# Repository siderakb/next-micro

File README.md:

# Next *μ*

**Next *μ*** or **Next Micro** is a Pro Micro/[Elite-C](https://deskthority.net/wiki/Elite-C) compatible ATmega32U4 board, specialized design for keyboards.

It has mid-mount USB Type-C and more available pins (25 pins, all pins of ATmega32U4 except `PE2/HWB`) than both Pro Micro (18 pins) and Elite-C (24 pins).  
The on-board RESET button makes development easier.

> A part of [ErgoSNM keyboard](https://github.com/siderakb/ergo-snm-keyboard) project.  

## Preview

| Front                           | Back                           | Layers                    |
| ------------------------------- | ------------------------------ | ------------------------- |
|  |  |  |

## Pinouts
| Func | 32U4  | L <-> R |  32U4 | Func |
| :--- | :---- | :-----: | ----: | ---: |
|      | PB7\* |         |   PB0 |      |
| TX   | PD3   |         |   RAW |      |
| RX   | PD2   |         |   GND |      |
|      | GND   |         | RESET |      |
|      | GND   |         |   VCC |      |
| SDA  | PD1   |         |   PF4 |   A3 |
| SCL  | PD0\* |         |   PF5 |   A2 |
| A6   | PD4   |         |   PF6 |   A1 |
|      | PC6\* |         |   PF7 |   A0 |
| A7   | PD7\* |         |   PB1 | SCLK |
|      | PE6   |         |   PB3 | MISO |
| A8   | PB4   |         |   PB2 | MOSI |
| A9   | PB5\* |         | PB6\* |  A10 |

Bottom row from left to right: PD6, PD5, PC7\*, PF1, PF0.

- The pin marked with `*` can output PWM.
- RAW: LDO Vin pin.

> The pinouts not fully compatible with Elite-C.

## Jumper Config

- JP1: LDO bypass.
  - Open: VCC is 3.3V (LDO Vout).
  - Closed: VCC is 5V (VBUS or RAW). 

## BOM

| Designator  | Value                   | Footprint                           |
| ----------- | ----------------------- | ----------------------------------- |
| C1,C2       | 20pF                    | 0402 (1005 Metric)                  |
| C3,C6,C7    | 100nF                   | 0402 (1005 Metric)                  |
| C4,C5,C8,C9 | 1uF                     | 0402 (1005 Metric)                  |
| D1          | B5817                   | SOD-323                             |
| F1          | 500mA, 6V               | 0805 (2012 Metric)                  |
| J1          | USB_C_Receptacle_USB2.0 | 918-418K2024S40000                  |
| R1,R2       | 5.1k                    | 0402 (1005 Metric)                  |
| R3,R4       | 22                      | 0402 (1005 Metric)                  |
| R5          | 10k                     | 0402 (1005 Metric)                  |
| SW1         | RESET                   | B3U-1000P                           |
| U1          | ATmega32U4-M            | QFN-44-1EP 7x7mm P0.5mm EP5.2x5.2mm |
| U2          | RT9013-33GB             | SOT-23-5                            |
| Y1          | 8MHz                    | 2Pin 5x3.2mm                        |
> See also [`doc/next-micro_bom.csv`](./doc/next-micro_bom.csv).

There is not designator silkscreen on PCB, please use your browser to open the `ibom.html` file (placed in [release page][release] and [`doc/`](./doc/)) to refer to the placement of the parts, it is generated by [Interactive HTML BOM](https://github.com/openscopeproject/InteractiveHtmlBom) plugin.

## PCBA

The BOM and CPL files for PCBA are placed in the [`doc/`](./doc/) folder and [release page][release].

## Board Characteristics

- Copper layer count: 2
- Board thickness: 1.6 mm
- Board overall dimensions: 17.78 x 33.02 mm (0.7 x 1.3 inch)
- Min track/spacing: 0.13 mm / 0.13 mm
- Min hole diameter: 0.3 mm
- Castellated pads: No
- Edge card connectors: No
- Plated board edge: No

## Disclaimer

These files without warranty of any kind, use at your own risk, it is recommended to check yourself before manufacture.

For the full statement, please see [LICENSE](./LICENSE).

[release]: https://github.com/ziteh/next-micro/releases

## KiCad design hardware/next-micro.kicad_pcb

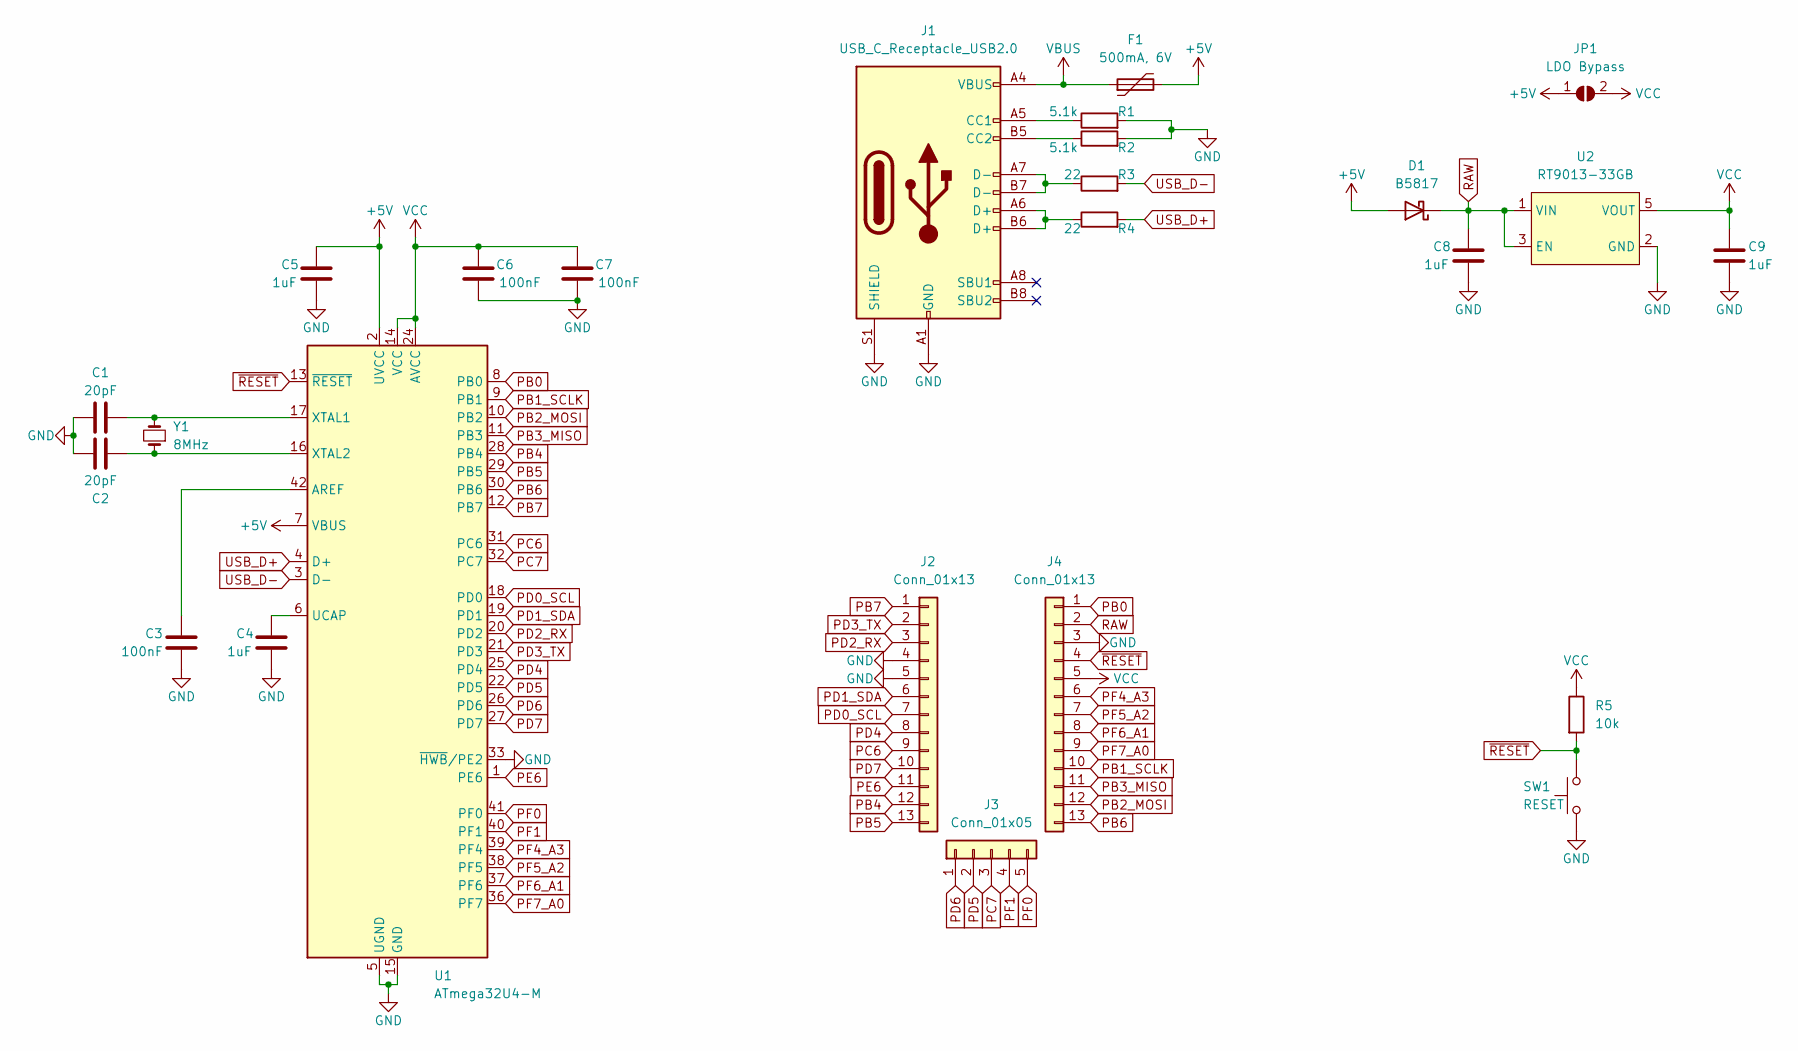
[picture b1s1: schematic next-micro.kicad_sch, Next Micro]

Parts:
C1, C2: 20pF; C_0402_1005Metric; MFR. Part # 0402CG200J500NT; JLCPCB Part # C1554
C3, C6, C7: 100nF; C_0402_1005Metric; MFR. Part # CL05B104KB54PNC; JLCPCB Part # C307331
C4, C5, C8, C9: 1uF; C_0402_1005Metric; MFR. Part # CL05A105KA5NQNC; JLCPCB Part # C52923
D1: B5817; D_SOD-323_HandSoldering; MFR. Part # B5817WS; JLCPCB Part # C123899
F1: 500mA, 6V; Fuse_0805_2012Metric; MFR. Part # SMD0805B050TF; JLCPCB Part # C269104
J1: USB_C_Receptacle_USB2.0; USB Type-C Mid-Mount Receptacle 16P; MFR. Part # 918-418K2024S40000; JLCPCB Part # C168688
J2, J4: Conn_01x13; PinHeader_1x13_P2.54mm_Vertical
J3: Conn_01x05; PinHeader_1x05_P2.54mm_Vertical
JP1: SolderJumper_2_Open; SolderJumper-2_P1.3mm_Open_TrianglePad1.0x1.5mm
R1, R2: 5.1k; R_0402_1005Metric; MFR. Part # 0402WGF5101TCE; JLCPCB Part # C25905
R3, R4: 22; R_0402_1005Metric; MFR. Part # 0402WGF220JTCE; JLCPCB Part # C25092
R5: 10k; R_0402_1005Metric; MFR. Part # 0402WGF1002TCE; JLCPCB Part # C25744
SW1: RESET; SW_SPST_B3U-1000P; MFR. Part # B3U-1000P; JLCPCB Part # C231329
U1: ATmega32U4-M; QFN-44-1EP_7x7mm_P0.5mm_EP5.2x5.2mm; MFR. Part # ATMEGA32U4-MU; JLCPCB Part # C112161
U2: RT9013-33GB; SOT-23-5; MFR. Part # RT9013-33GB; JLCPCB Part # C47773
Y1: 8MHz; Crystal_SMD_Qantek_QC5CB-2Pin_5x3.2mm; MFR. Part # X50328MSB2GI; JLCPCB Part # C115962

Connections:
+5V: C5.1, D1.2 (A), F1.2, JP1.1 (A), U1.2 (UVCC), U1.7 (VBUS)
GND: C1.1, C2.1, C3.1, C4.2, C5.2, C6.1, C7.1, C8.2, C9.2, J1.A1 (GND), J1.A12 (GND), J1.B1 (GND), J1.B12 (GND), J1.S1 (SHIELD), J2.4, J2.5, J4.3, R1.2, R2.2, SW1.1, U1.5 (UGND), U1.15 (GND), U1.23 (GND), U1.33 (~HWB/PE2), U1.35 (GND), U1.43 (GND), U1.45 (GND), U2.2 (GND)
unnamed: C1.2, U1.17 (XTAL1), Y1.2
unnamed: C2.2, U1.16 (XTAL2), Y1.1
unnamed: C3.2, U1.42 (AREF)
unnamed: C4.1, U1.6 (UCAP)
unnamed: J1.A5 (CC1), R1.1
unnamed: J1.A6 (D+), J1.B6 (D+), R4.1
unnamed: J1.A7 (D-), J1.B7 (D-), R3.1
unnamed: J1.B5 (CC2), R2.1
PB0: J4.1, U1.8 (PB0)
PB1_SCLK: J4.10, U1.9 (PB1)
PB2_MOSI: J4.12, U1.10 (PB2)
PB3_MISO: J4.11, U1.11 (PB3)
PB4: J2.12, U1.28 (PB4)
PB5: J2.13, U1.29 (PB5)
PB6: J4.13, U1.30 (PB6)
PB7: J2.1, U1.12 (PB7)
PC6: J2.9, U1.31 (PC6)
PC7: J3.3, U1.32 (PC7)
PD0_SCL: J2.7, U1.18 (PD0)
PD1_SDA: J2.6, U1.19 (PD1)
PD2_RX: J2.3, U1.20 (PD2)
PD3_TX: J2.2, U1.21 (PD3)
PD4: J2.8, U1.25 (PD4)
PD5: J3.2, U1.22 (PD5)
PD6: J3.1, U1.26 (PD6)
PD7: J2.10, U1.27 (PD7)
PE6: J2.11, U1.1 (PE6)
PF0: J3.5, U1.41 (PF0)
PF1: J3.4, U1.40 (PF1)
PF4_A3: J4.6, U1.39 (PF4)
PF5_A2: J4.7, U1.38 (PF5)
PF6_A1: J4.8, U1.37 (PF6)
PF7_A0: J4.9, U1.36 (PF7)
RAW: C8.1, D1.1 (K), J4.2, U2.1 (VIN), U2.3 (EN)
USB_D+: R4.2, U1.4 (D+)
USB_D-: R3.2, U1.3 (D-)
VBUS: F1.1, J1.A4 (VBUS), J1.A9 (VBUS), J1.B4 (VBUS), J1.B9 (VBUS)
VCC: C6.2, C7.2, C9.1, J4.5, JP1.2 (B), R5.1, U1.14 (VCC), U1.24 (AVCC), U1.34 (VCC), U1.44 (AVCC), U2.5 (VOUT)
~RESET: J4.4, R5.2, SW1.2, U1.13 (~RESET)

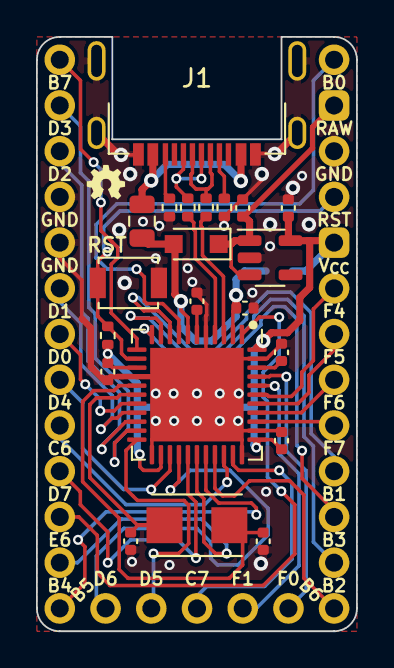
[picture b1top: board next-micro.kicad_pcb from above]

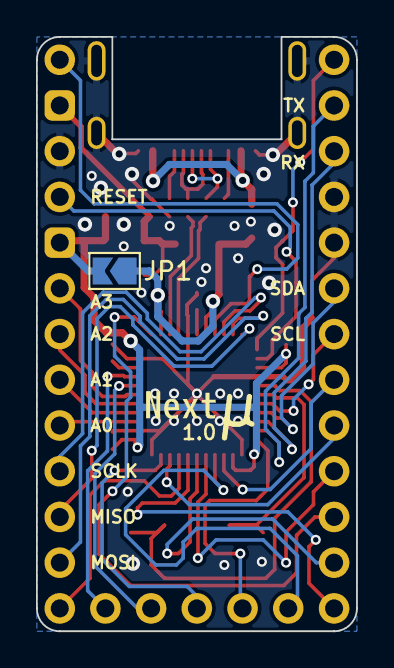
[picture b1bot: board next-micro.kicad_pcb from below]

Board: 2 copper layers, 17.8 x 33.0 mm, 26 parts (4 on the bottom side), 41 nets.

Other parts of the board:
kibuzzard-637F2329: G***; kibuzzard-637F2329

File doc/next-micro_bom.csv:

Comment,Designator,Footprint,JLCPCB Part #
"20pF","C1,C2","Capacitor_SMD:C_0402_1005Metric","C1554"
"100nF","C3,C6,C7","Capacitor_SMD:C_0402_1005Metric","C307331"
"1uF","C4,C5,C8,C9","Capacitor_SMD:C_0402_1005Metric","C52923"
"B5817","D1","Diode_SMD:D_SOD-323","C123899"
"500mA, 6V","F1","Fuse:Fuse_0805_2012Metric","C269104"
"USB_C_Receptacle_USB2.0","J1","next_micro:USB Type-C Mid-Mount Receptacle 16P","C168688"
"5.1k","R1,R2","Resistor_SMD:R_0402_1005Metric","C25905"
"22","R3,R4","Resistor_SMD:R_0402_1005Metric","C25092"
"10k","R5","Resistor_SMD:R_0402_1005Metric","C25744"
"RESET","SW1","Button_Switch_SMD:SW_SPST_B3U-1000P","C231329"
"ATmega32U4-M","U1","Package_DFN_QFN:QFN-44-1EP_7x7mm_P0.5mm_EP5.2x5.2mm","C112161"
"RT9013-33GB","U2","Package_TO_SOT_SMD:SOT-23-5","C47773"
"8MHz","Y1","Crystal:Crystal_SMD_Qantek_QC5CB-2Pin_5x3.2mm","C115962"

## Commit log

2022-11-24 init commit
2022-11-24 Add README.md
2022-11-24 Fix path
2022-11-24 Add license file
2022-11-24 Add PCBA files and move files
2022-12-07 Replace D1 footprint to hand soldering version
2022-12-07 Update CPL
2022-12-07 Update date
2023-04-29 Add footprint library path table
2023-06-25 Update URL, replace "ziteh" with "siderakb".

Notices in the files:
hardware/next-micro.kicad_pcb:
MIT License (Open source hardware)
